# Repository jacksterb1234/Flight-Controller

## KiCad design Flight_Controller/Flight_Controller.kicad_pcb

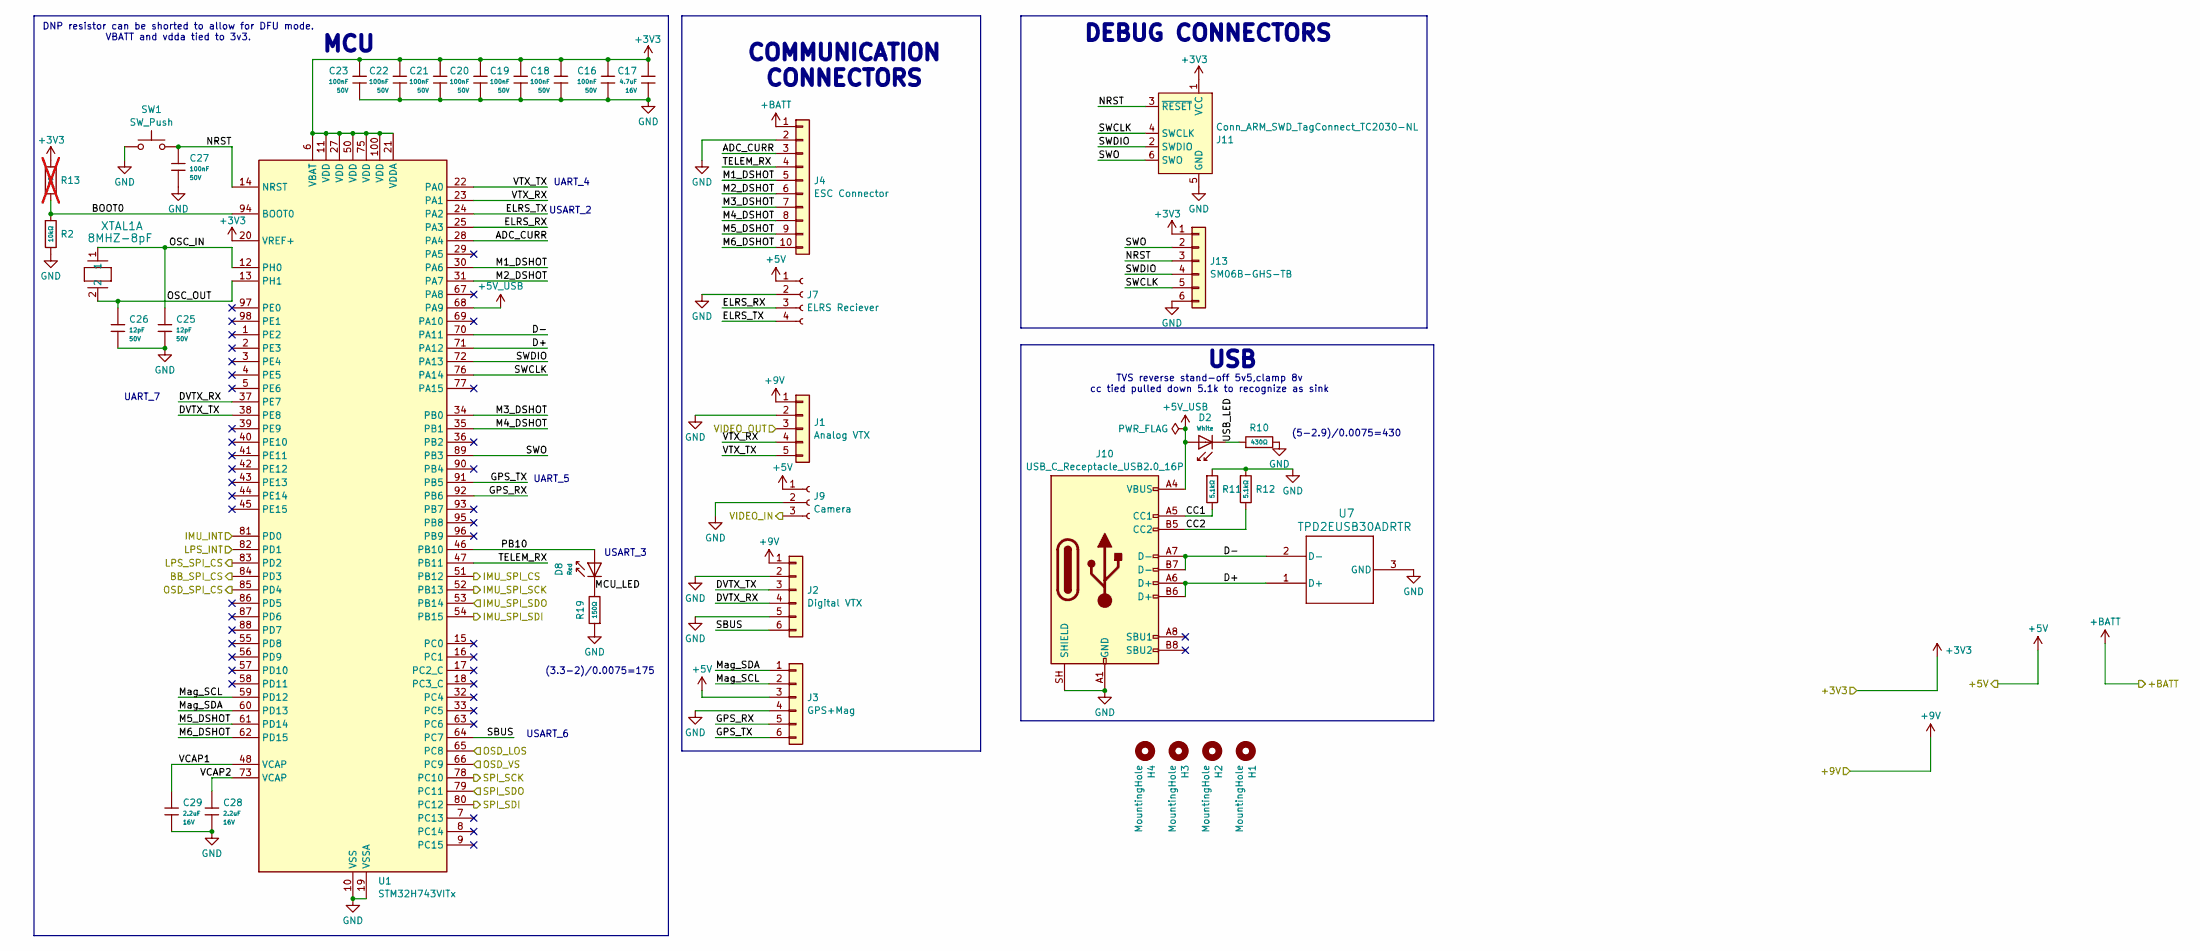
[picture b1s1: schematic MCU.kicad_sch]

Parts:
C16, C18, C19, C20, C21, C22, C23, C27: 100nF; C_0603; Voltage Rated 50V; Tolerance ±10%; Part CC0603KRX7R9BB104; LCSC C14663
C17: 4.7uF; C_0603; Voltage Rated 16V; Tolerance ±10%; Part CL10A475KO8NNNC; LCSC C19666
C25, C26: 12pF; C_0603; Voltage Rated 50V; Tolerance ±5%; Part CL10C120JB8NNNC; LCSC C38523
C28, C29: 2.2uF; C_0603; Voltage Rated 16V; Tolerance ±10%; Part CL10A225KO8NNNC; LCSC C23630
D2: White; D_0603; Part KT-0603W; LCSC C2290
D8: Red; D_0603; Part KT-0603R; LCSC C2286
H1, H2, H3, H4: MountingHole; MountingHole_3.2mm_M3_Pad_Via
J1: Analog VTX; JST_SH_SM05B-SRSS-TB_1x05-1MP_P1.00mm_Horizontal
J2: Digital VTX; JST_SH_SM06B-SRSS-TB_1x06-1MP_P1.00mm_Horizontal
J3: GPS+Mag; JST_SH_SM06B-SRSS-TB_1x06-1MP_P1.00mm_Horizontal
J4: ESC Connector; JST_SH_SM10B-SRSS-TB_1x10-1MP_P1.00mm_Horizontal
J7: ELRS Reciever; JST_SH_SM04B-SRSS-TB_1x04-1MP_P1.00mm_Horizontal
J9: Camera; JST_SH_SM03B-SRSS-TB_1x03-1MP_P1.00mm_Horizontal
J10: USB_C_Receptacle_USB2.0_16P; USB_C_Receptacle_GCT_USB4110
J11: Conn_ARM_SWD_TagConnect_TC2030-NL; Tag-Connect_TC2030-IDC-NL_2x03_P1.27mm_Vertical
J13: SM06B-GHS-TB; JST_GH_SM06B-GHS-TB_1x06-1MP_P1.25mm_Horizontal
R2: 10kΩ; R_0603; Overload Voltage (Max) 75V; Tolerance ±1%; Part 0603WAF1002T5E; LCSC C25804
R10: 430Ω; R_0603; Overload Voltage (Max) 75V; Tolerance ±1%; Part 0603WAF4300T5E; LCSC C23170
R11, R12: 5.1kΩ; R_0603; Overload Voltage (Max) 75V; Tolerance ±1%; Part 0603WAF5101T5E; LCSC C23186
R13: 0Ω; R_0603; Overload Voltage (Max) 75V; Tolerance ±1%; Part 0603WAF0000T5E; LCSC C21189; not fitted
R19: 150Ω; R_0603; Overload Voltage (Max) 75V; Tolerance ±1%; Part 0603WAF1500T5E; LCSC C22808
SW1: SW_Push; SW_TS-1088-AR02016
U1: STM32H743VITx; LQFP-100_14x14mm_P0.5mm
U7: TPD2EUSB30ADRTR; DRT3-L
XTAL1: 8MHZ-8pF; XTAL_NX3225GD-8MHZ-STD-CRA-3_NDK-L

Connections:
+3V3: C16.1, C17.1, C18.1, C19.1, C20.1, C21.1, C22.1, C23.1, J11.1 (VCC), J13.1, R13.1, U1.6 (VBAT), U1.11 (VDD), U1.20 (VREF+), U1.21 (VDDA), U1.27 (VDD), U1.50 (VDD), U1.75 (VDD), U1.100 (VDD); also elsewhere on the board
+5V: J3.3, J7.1, J9.1; also elsewhere on the board
+5V_USB: D2.2, J10.A4 (VBUS), J10.A9 (VBUS), J10.B4 (VBUS), J10.B9 (VBUS), U1.68 (PA9)
+9V: J1.1, J2.1; also elsewhere on the board
+BATT: J4.1; also elsewhere on the board
/MCU/Connectors/ADC_CURR: J4.3, U1.28 (PA4)
/MCU/Connectors/BB_SPI_CS: U1.84 (PD3); also elsewhere on the board
/MCU/Connectors/BOOT0: R2.1, R13.2, U1.94 (BOOT0)
/MCU/Connectors/CC1: J10.A5 (CC1), R11.2
/MCU/Connectors/CC2: J10.B5 (CC2), R12.2
/MCU/Connectors/D+: J10.A6 (D+), J10.B6 (D+), U1.71 (PA12), U7.1 (D+)
/MCU/Connectors/D-: J10.A7 (D-), J10.B7 (D-), U1.70 (PA11), U7.2 (D-)
/MCU/Connectors/DVTX_RX: J2.4, U1.37 (PE7)
/MCU/Connectors/DVTX_TX: J2.3, U1.38 (PE8)
/MCU/Connectors/ELRS_RX: J7.3, U1.25 (PA3)
/MCU/Connectors/ELRS_TX: J7.4, U1.24 (PA2)
/MCU/Connectors/GPS_RX: J3.5, U1.92 (PB6)
/MCU/Connectors/GPS_TX: J3.6, U1.91 (PB5)
/MCU/Connectors/IMU_INT: U1.81 (PD0); also elsewhere on the board
/MCU/Connectors/IMU_SPI_CS: U1.51 (PB12); also elsewhere on the board
/MCU/Connectors/IMU_SPI_SCK: U1.52 (PB13); also elsewhere on the board
/MCU/Connectors/IMU_SPI_SDI: U1.54 (PB15); also elsewhere on the board
/MCU/Connectors/IMU_SPI_SDO: U1.53 (PB14); also elsewhere on the board
/MCU/Connectors/LPS_INT: U1.82 (PD1); also elsewhere on the board
/MCU/Connectors/LPS_SPI_CS: U1.83 (PD2); also elsewhere on the board
/MCU/Connectors/M1_DSHOT: J4.5, U1.30 (PA6)
/MCU/Connectors/M2_DSHOT: J4.6, U1.31 (PA7)
/MCU/Connectors/M3_DSHOT: J4.7, U1.34 (PB0)
/MCU/Connectors/M4_DSHOT: J4.8, U1.35 (PB1)
/MCU/Connectors/M5_DSHOT: J4.9, U1.61 (PD14)
/MCU/Connectors/M6_DSHOT: J4.10, U1.62 (PD15)
/MCU/Connectors/MCU_LED: D8.1, R19.2
/MCU/Connectors/Mag_SCL: J3.2, U1.59 (PD12)
/MCU/Connectors/Mag_SDA: J3.1, U1.60 (PD13)
/MCU/Connectors/NRST: C27.2, J11.3 (~RESET), J13.3, SW1.2, U1.14 (NRST)
/MCU/Connectors/OSC_IN: C25.2, U1.12 (PH0), XTAL1.1
/MCU/Connectors/OSC_OUT: C26.2, U1.13 (PH1), XTAL1.2
/MCU/Connectors/OSD_LOS: U1.65 (PC8); also elsewhere on the board
/MCU/Connectors/OSD_SPI_CS: U1.85 (PD4); also elsewhere on the board
/MCU/Connectors/OSD_VS: U1.66 (PC9); also elsewhere on the board
/MCU/Connectors/PB10: D8.2, U1.46 (PB10)
/MCU/Connectors/SBUS: J2.6, U1.64 (PC7)
/MCU/Connectors/SPI_SCK: U1.78 (PC10); also elsewhere on the board
/MCU/Connectors/SPI_SDI: U1.80 (PC12); also elsewhere on the board
/MCU/Connectors/SPI_SDO: U1.79 (PC11); also elsewhere on the board
/MCU/Connectors/SWCLK: J11.4 (SWCLK), J13.5, U1.76 (PA14)
/MCU/Connectors/SWDIO: J11.2 (SWDIO), J13.4, U1.72 (PA13)
/MCU/Connectors/SWO: J11.6 (SWO), J13.2, U1.89 (PB3)
/MCU/Connectors/TELEM_RX: J4.4, U1.47 (PB11)
/MCU/Connectors/USB_LED: D2.1, R10.1
/MCU/Connectors/VCAP1: C29.1, U1.48 (VCAP)
/MCU/Connectors/VCAP2: C28.1, U1.73 (VCAP)
/MCU/Connectors/VIDEO_IN: J9.3; also elsewhere on the board
/MCU/Connectors/VIDEO_OUT: J1.3; also elsewhere on the board
/MCU/Connectors/VTX_RX: J1.4, U1.23 (PA1)
/MCU/Connectors/VTX_TX: J1.5, U1.22 (PA0)
GND: C16.2, C17.2, C18.2, C19.2, C20.2, C21.2, C22.2, C23.2, C25.1, C26.1, C27.1, C28.2, C29.2, J1.2, J2.2, J2.5, J3.4, J4.2, J7.2, J9.2, J10.A1 (GND), J10.A12 (GND), J10.B1 (GND), J10.B12 (GND), J10.SH (SHIELD), J11.5 (GND), J13.6, R2.2, R10.2, R11.1, R12.1, R19.1, SW1.1, U1.10 (VSS), U1.19 (VSSA), U1.26 (VSS), U1.49 (VSS), U1.74 (VSS), U1.99 (VSS), U7.3 (GND); also elsewhere on the board

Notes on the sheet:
UART_4
UART_7
TVS reverse stand-off 5v5,clamp 8v cc tied pulled down 5.1k to recognize as sink
UART_5
COMMUNICATION CONNECTORS
(5-2.9)/0.0075=430
USART_3
USB
(3.3-2)/0.0075=175
MCU
USART_6
DEBUG CONNECTORS
USART_2
DNP resistor can be shorted to allow for DFU mode. VBATT and vdda tied to 3v3.

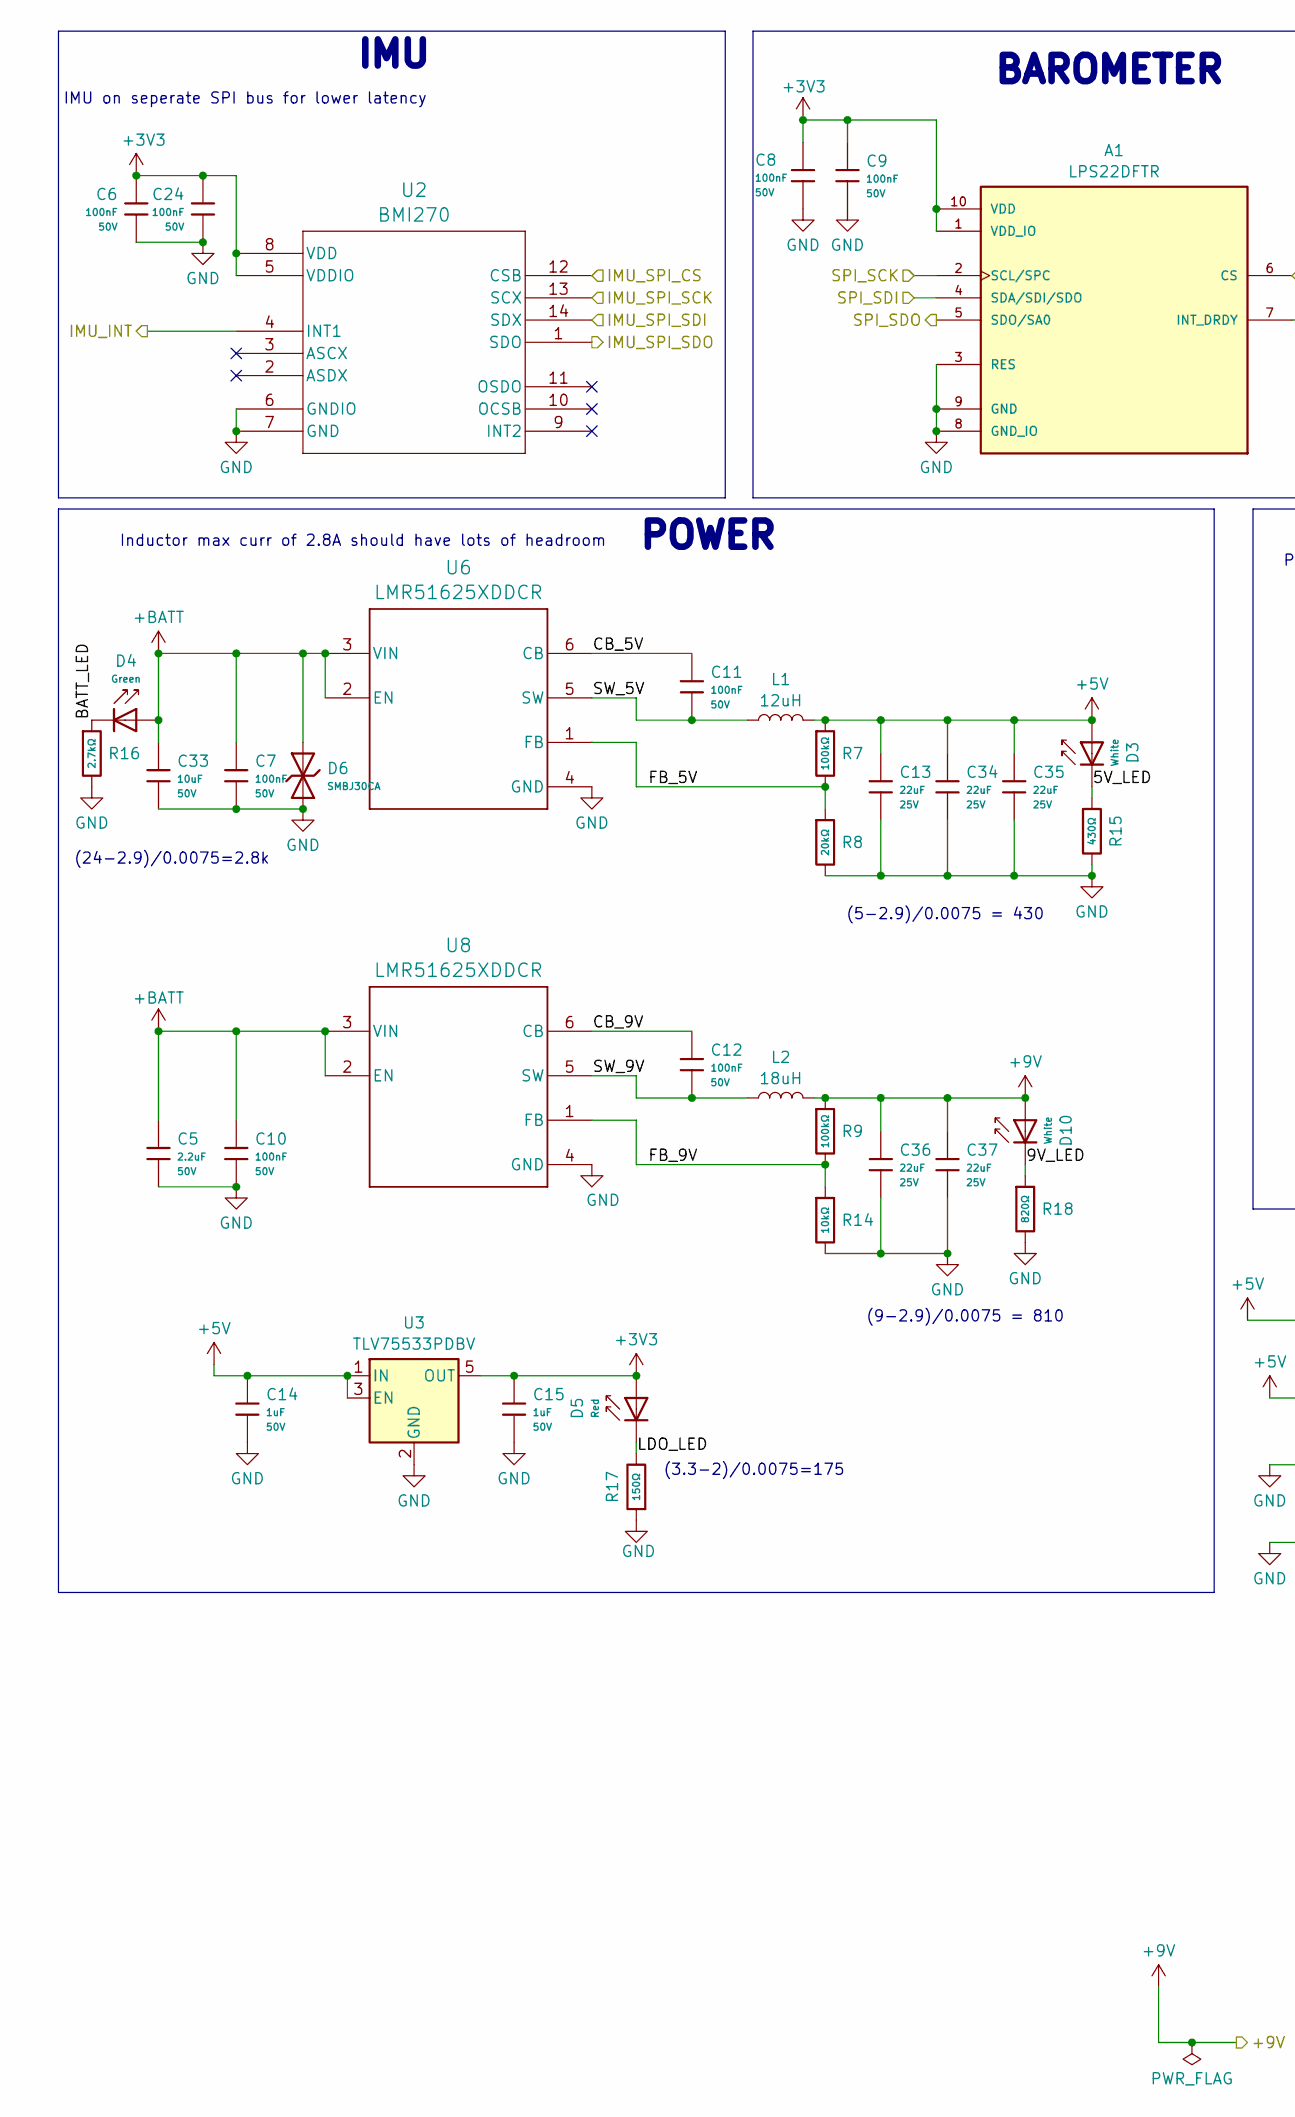
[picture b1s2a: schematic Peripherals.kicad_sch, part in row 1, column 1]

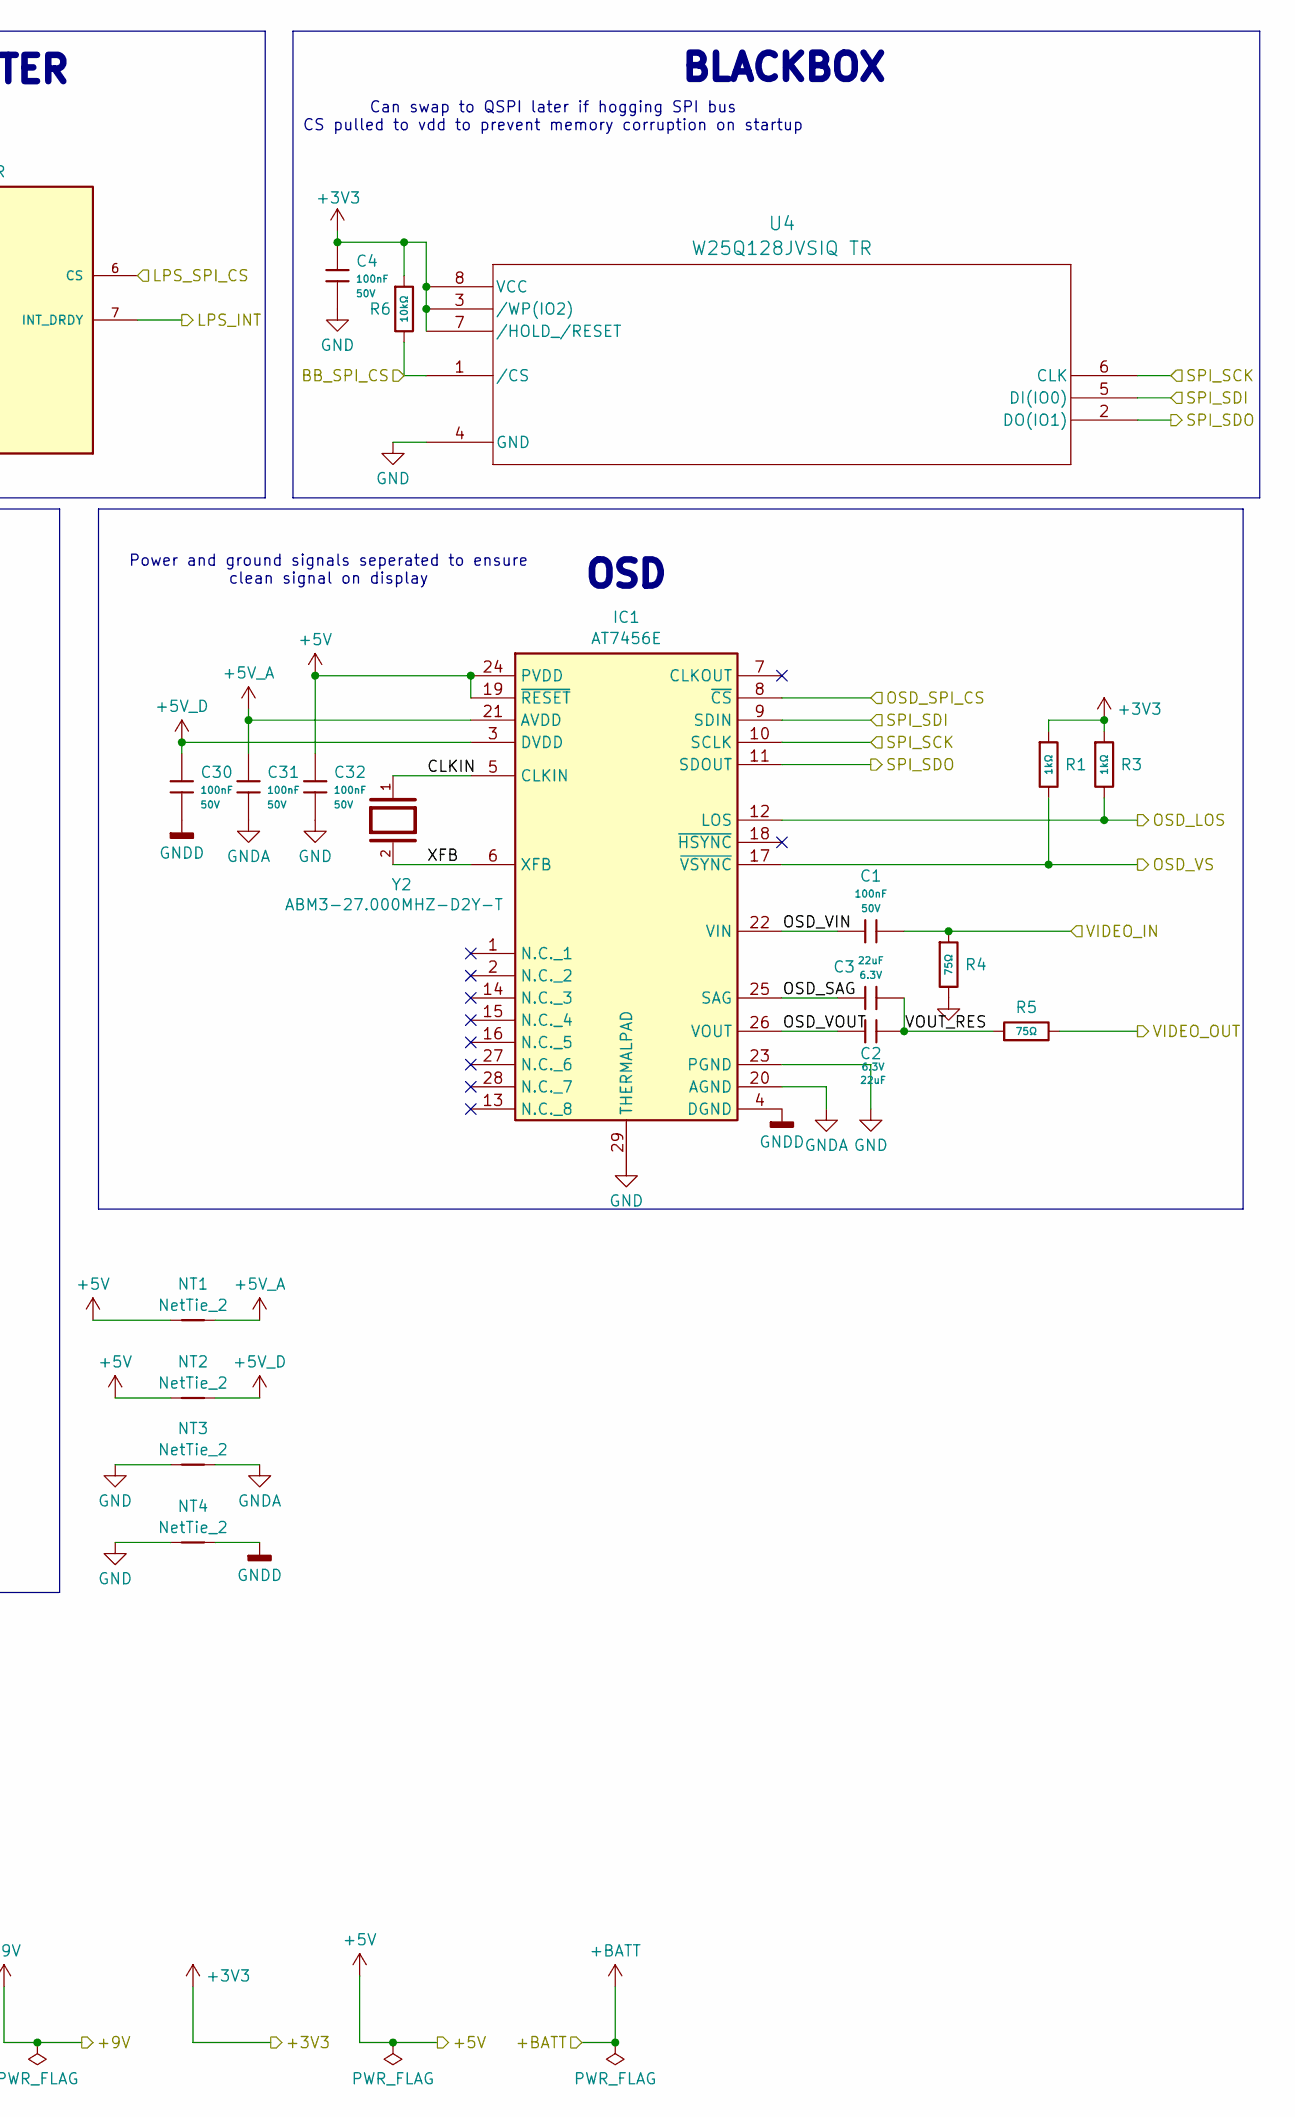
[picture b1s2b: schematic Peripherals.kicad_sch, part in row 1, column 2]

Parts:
A1: LPS22DFTR; XDCR_LPS22DFTR; PARTREV 3
C1, C4, C6, C7, C8, C9, C10, C11, C12, C24, C30, C31, C32: 100nF; C_0603; Voltage Rated 50V; Tolerance ±10%; Part CC0603KRX7R9BB104; LCSC C14663
C2, C3: 22uF; C_0603; Voltage Rated 6.3V; Tolerance ±20%; Part CL10A226MQ8NRNC; LCSC C59461
C5: 2.2uF; C_0805; Voltage Rated 50V; Tolerance ±10%; Part CL21A225KBQNNNE; LCSC C377773
C13, C34, C35, C36, C37: 22uF; C_1206; Voltage Rated 25V; Tolerance ±10%; Part CL31A226KAHNNNE; LCSC C12891
C14, C15: 1uF; C_0603; Voltage Rated 50V; Tolerance ±10%; Part CL10A105KB8NNNC; LCSC C15849
C33: 10uF; C_0805; Voltage Rated 50V; Tolerance ±10%; Part GRM21BR61H106KE43L; LCSC C440198
D3, D10: White; D_0603; Part KT-0603W; LCSC C2290
D4: Green; D_0805; Part KT-0805G; LCSC C2297
D5: Red; D_0603; Part KT-0603R; LCSC C2286
D6: SMBJ30CA; D_SMB; Clamping Voltage 48.4V; Voltage - Breakdown 36.8V; Part SMBJ30CA; LCSC C19077585
IC1: AT7456E; SOP65P640X120-29N; Manufacturer_Part_Number AT7456E
L1: 12uH; L_TDK_VLS6045EX_VLS6045AF
L2: 18uH; L_TDK_VLP8040
NT1, NT2, NT3, NT4: NetTie_2; NetTie-2_SMD_Pad0.5mm
R1, R3: 1kΩ; R_0603; Overload Voltage (Max) 75V; Tolerance ±1%; Part 0603WAF1001T5E; LCSC C21190
R4, R5: 75Ω; R_0603; Overload Voltage (Max) 75V; Tolerance ±1%; Part 0603WAF750JT5E; LCSC C4275
R6, R14: 10kΩ; R_0603; Overload Voltage (Max) 75V; Tolerance ±1%; Part 0603WAF1002T5E; LCSC C25804
R7, R9: 100kΩ; R_0603; Overload Voltage (Max) 75V; Tolerance ±1%; Part 0603WAF1003T5E; LCSC C25803
R8: 20kΩ; R_0603; Overload Voltage (Max) 75V; Tolerance ±1%; Part 0603WAF2002T5E; LCSC C4184
R15: 430Ω; R_0603; Overload Voltage (Max) 75V; Tolerance ±1%; Part 0603WAF4300T5E; LCSC C23170
R16: 2.7kΩ; R_0603; Overload Voltage (Max) 75V; Tolerance ±1%; Part 0603WAF2701T5E; LCSC C13167
R17: 150Ω; R_0603; Overload Voltage (Max) 75V; Tolerance ±1%; Part 0603WAF1500T5E; LCSC C22808
R18: 820Ω; R_0603; Overload Voltage (Max) 75V; Tolerance ±1%; Part 0603WAF8200T5E; LCSC C23253
U2: BMI270; BMI270_BOS-L
U3: TLV75533PDBV; SOT-23-5
U4: W25Q128JVSIQ TR; SOIC_208MIL_WIN-L
U6, U8: LMR51625XDDCR; DDC0006A-MFG
Y2: ABM3-27.000MHZ-D2Y-T; XTAL_ABM3-27.000MHZ-D2Y-T; PARTREV 4/25/2022

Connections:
+3V3: A1.1 (VDD_IO), A1.10 (VDD), C4.1, C6.1, C8.1, C9.1, C15.1, C24.1, D5.2, R1.1, R3.1, R6.1, U2.5 (VDDIO), U2.8 (VDD), U3.5 (OUT), U4.3 (/WP(IO2)), U4.7 (/HOLD_/RESET), U4.8 (VCC); also elsewhere on the board
+5V: C13.1, C14.1, C32.1, C34.1, C35.1, D3.2, IC1.19 (~RESET), IC1.24 (PVDD), L1.2, NT1.2, NT2.2, R7.1, U3.1 (IN), U3.3 (EN); also elsewhere on the board
+5V_A: C31.1, IC1.21 (AVDD), NT1.1
+5V_D: C30.1, IC1.3 (DVDD), NT2.1
+9V: C36.1, C37.1, D10.2, L2.2, R9.1; also elsewhere on the board
+BATT: C5.1, C7.1, C10.1, C33.1, D4.2, D6.2, U6.2 (EN), U6.3 (VIN), U8.2 (EN), U8.3 (VIN); also elsewhere on the board
/MCU/Connectors/BB_SPI_CS: R6.2, U4.1 (/CS); also elsewhere on the board
/MCU/Connectors/IMU_INT: U2.4 (INT1); also elsewhere on the board
/MCU/Connectors/IMU_SPI_CS: U2.12 (CSB); also elsewhere on the board
/MCU/Connectors/IMU_SPI_SCK: U2.13 (SCX); also elsewhere on the board
/MCU/Connectors/IMU_SPI_SDI: U2.14 (SDX); also elsewhere on the board
/MCU/Connectors/IMU_SPI_SDO: U2.1 (SDO); also elsewhere on the board
/MCU/Connectors/LPS_INT: A1.7 (INT_DRDY); also elsewhere on the board
/MCU/Connectors/LPS_SPI_CS: A1.6 (CS); also elsewhere on the board
/MCU/Connectors/OSD_LOS: IC1.12 (LOS), R3.2; also elsewhere on the board
/MCU/Connectors/OSD_SPI_CS: IC1.8 (~CS); also elsewhere on the board
/MCU/Connectors/OSD_VS: IC1.17 (~VSYNC), R1.2; also elsewhere on the board
/MCU/Connectors/SPI_SCK: A1.2 (SCL/SPC), IC1.10 (SCLK), U4.6 (CLK); also elsewhere on the board
/MCU/Connectors/SPI_SDI: A1.4 (SDA/SDI/SDO), IC1.9 (SDIN), U4.5 (DI(IO0)); also elsewhere on the board
/MCU/Connectors/SPI_SDO: A1.5 (SDO/SA0), IC1.11 (SDOUT), U4.2 (DO(IO1)); also elsewhere on the board
/MCU/Connectors/VIDEO_IN: C1.2, R4.1; also elsewhere on the board
/MCU/Connectors/VIDEO_OUT: R5.2; also elsewhere on the board
/Peripherals/Power/5V_LED: D3.1, R15.1
/Peripherals/Power/9V_LED: D10.1, R18.1
/Peripherals/Power/BATT_LED: D4.1, R16.1
/Peripherals/Power/CB_5V: C11.1, U6.6 (CB)
/Peripherals/Power/CB_9V: C12.1, U8.6 (CB)
/Peripherals/Power/CLKIN: IC1.5 (CLKIN), Y2.1
/Peripherals/Power/FB_5V: R7.2, R8.1, U6.1 (FB)
/Peripherals/Power/FB_9V: R9.2, R14.1, U8.1 (FB)
/Peripherals/Power/LDO_LED: D5.1, R17.2
/Peripherals/Power/OSD_SAG: C3.1, IC1.25 (SAG)
/Peripherals/Power/OSD_VIN: C1.1, IC1.22 (VIN)
/Peripherals/Power/OSD_VOUT: C2.1, IC1.26 (VOUT)
/Peripherals/Power/SW_5V: C11.2, L1.1, U6.5 (SW)
/Peripherals/Power/SW_9V: C12.2, L2.1, U8.5 (SW)
/Peripherals/Power/VOUT_RES: C2.2, C3.2, R5.1
/Peripherals/Power/XFB: IC1.6 (XFB), Y2.2
GND: A1.3 (RES), A1.8 (GND_IO), A1.9 (GND), C4.2, C5.2, C6.2, C7.2, C8.2, C9.2, C10.2, C13.2, C14.2, C15.2, C24.2, C32.2, C33.2, C34.2, C35.2, C36.2, C37.2, D6.1, IC1.23 (PGND), IC1.29 (THERMALPAD), NT3.2, NT4.2, R4.2, R8.2, R14.2, R15.2, R16.2, R17.1, R18.2, U2.6 (GNDIO), U2.7 (GND), U3.2 (GND), U4.4 (GND), U6.4 (GND), U8.4 (GND); also elsewhere on the board
GNDA: C31.2, IC1.20 (AGND), NT3.1
GNDD: C30.2, IC1.4 (DGND), NT4.1

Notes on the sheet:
Inductor max curr of 2.8A should have lots of headroom
(5-2.9)/0.0075 = 430
(24-2.9)/0.0075=2.8k
Can swap to QSPI later if hogging SPI bus CS pulled to vdd to prevent memory corruption on startup
Power and ground signals seperated to ensure clean signal on display
(3.3-2)/0.0075=175
POWER
IMU on seperate SPI bus for lower latency
OSD
(9-2.9)/0.0075 = 810
IMU
BAROMETER
BLACKBOX

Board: 4 copper layers, 94 parts (1 on the bottom side), 77 nets, no tracks yet.
